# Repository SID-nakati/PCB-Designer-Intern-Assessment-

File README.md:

# PCB-Designer-Intern-Assessment-
This repository contains the complete submission for the internship assessment, covering both hardware (PCB design) and software (embedded C coding) tasks.
1) Hardware - STM32 PCB Module Design:
--------------------------------------
- The PCB design was created using KiCad.
- The module is based on the STM32G series MCU.
- It includes:
   * SuperSpeed USB-C connector for power delivery and data transfer.
   * 4-pin SWD debugger connector.
   * Two 4-pin connectors for sensors (I2C and UART).
   * One LED connected to a GPIO pin for board bring-up.
- All the required files for the PCB design are located in the "hardware" folder.
- This folder contains:
   * Schematic design files (.kicad_sch)
   * PCB layout files (.kicad_pcb)
   * Symbol and footprint libraries
   * Gerber files for manufacturing
   * Bill of Materials (BOM)
   * Electrical Rule Check (ERC) and Design Rule Check (DRC) report files

2) Software - Embedded C / C++ Projects:
-----------------------------------------
- The "software" folder contains:
   * A C++ program file to reverse the words in a string.
   * A C++ program file to blink an LED at three different speeds in a continuous cycle.
   * A video demonstrating the LED blinking simulation on Tinkercad.

All source codes are well commented explaining the key logic.

-------------------------------
Thank you for reviewing my submission.

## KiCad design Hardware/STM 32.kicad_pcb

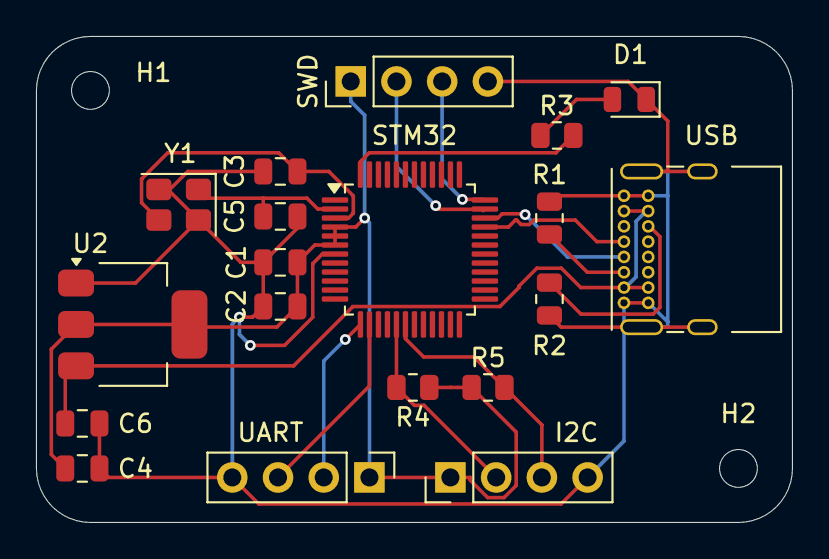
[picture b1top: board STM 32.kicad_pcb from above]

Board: 2 copper layers, 42.0 x 27.0 mm, 21 parts (0 on the bottom side), 17 nets.

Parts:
C1, C2: 100nF; C_0805_2012Metric
C3: 20pf; C_0805_2012Metric
C4, C6: 22uF; C_0805_2012Metric
C5: 20pF; C_0805_2012Metric
D1: LED; LED_0805_2012Metric
H1, H2: MountingHole; MountingHole_2.1mm
I2C: I2C; PinHeader_1x04_P2.54mm_Vertical
R1, R2: 5.1k; R_0805_2012Metric
R3: 330; R_0805_2012Metric
R4, R5: 4.7k; R_0805_2012Metric
STM32: STM32G0B1CBTx; LQFP-48_7x7mm_P0.5mm
SWD: SWD Debugger; PinHeader_1x04_P2.54mm_Vertical
U2: Voltage Regulator; SOT-223-3_TabPin2
UART: UART; PinHeader_1x04_P2.54mm_Vertical
USB: USB 2.0; USB_C_Receptacle_GCT_USB4085
Y1: 16MHz; Crystal_SMD_3225-4Pin_3.2x2.5mm

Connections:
/I2C_SCL: I2C.3, R5.2, STM32.18 (PA7)
/I2C_SDA: I2C.2, R4.2, STM32.17 (PA6)
/LED: R3.2, STM32.48 (PB9)
/OSC_IN: C5.1, STM32.2 (PC14), Y1.1
/OSC_OUT: C3.1, STM32.3 (PC15), Y1.3
/R_LED: D1.2 (A), R3.1
/SWCLK: STM32.36 (PA14), SWD.3
/SWDIO: STM32.35 (PA13), SWD.2
/UART_RX: STM32.14 (PA3), UART.3
/UART_TX: STM32.13 (PA2), UART.2
/USB_D+: STM32.34 (PA10/PA12), USB.A6 (D+)
/USB_D-: STM32.33 (PA9/PA11), USB.A7 (D-)
/USB_Det1: R1.1, USB.A5 (CC1)
/USB_Det2: R2.2, USB.B5 (CC2)
/VCC: C1.1, C2.1, C4.1, I2C.1, R4.1, R5.1, STM32.4 (VBAT), STM32.5 (VREF+), STM32.6 (VDD), SWD.1, U2.2 (VO), UART.1
GND: C1.2, C2.2, C3.2, C4.2, C5.2, C6.2, D1.1 (K), I2C.4, R1.2, R2.1, STM32.7 (VSS), SWD.4, U2.1 (GND), UART.4, USB.A1 (GND), USB.A12 (GND), USB.B1 (GND), USB.B12 (GND), USB.S1 (SHIELD), Y1.2, Y1.4
VBUS: C6.1, U2.3 (VI), USB.A4 (VBUS), USB.A9 (VBUS), USB.B4 (VBUS), USB.B9 (VBUS)

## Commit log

2025-06-11 Create Hardware
2025-06-11 Create tmp
